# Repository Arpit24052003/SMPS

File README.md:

# SMPS
Power Supply Unit (PSU) is a vital part in any electronic product design. Most household electronic products like Mobile Chargers, Bluetooth Speakers, Power Banks, Smart Watches etc requires a Power Supply circuit that could convert the AC mains supply to 5V DC to operate them. In this project we will build a similar AC to DC power supply circuit with 10W power rating. That is our circuit will convert the 220V AC mains to 5V and provide a maximum output current upto 2A. This power rating should be enough to power most electronic products running on 5V. Also 5V 2A SMPS circuit is quite popular in electronics since there are lots of microcontrollers which operates on 5V.

The idea of the project is to keep the build as simple as possible, hence we will design the complete circuit over a dotted board (perf board) and will also build our own transformer so that anyone could replicate this design or build similar ones. Excited Right! So lets get started.

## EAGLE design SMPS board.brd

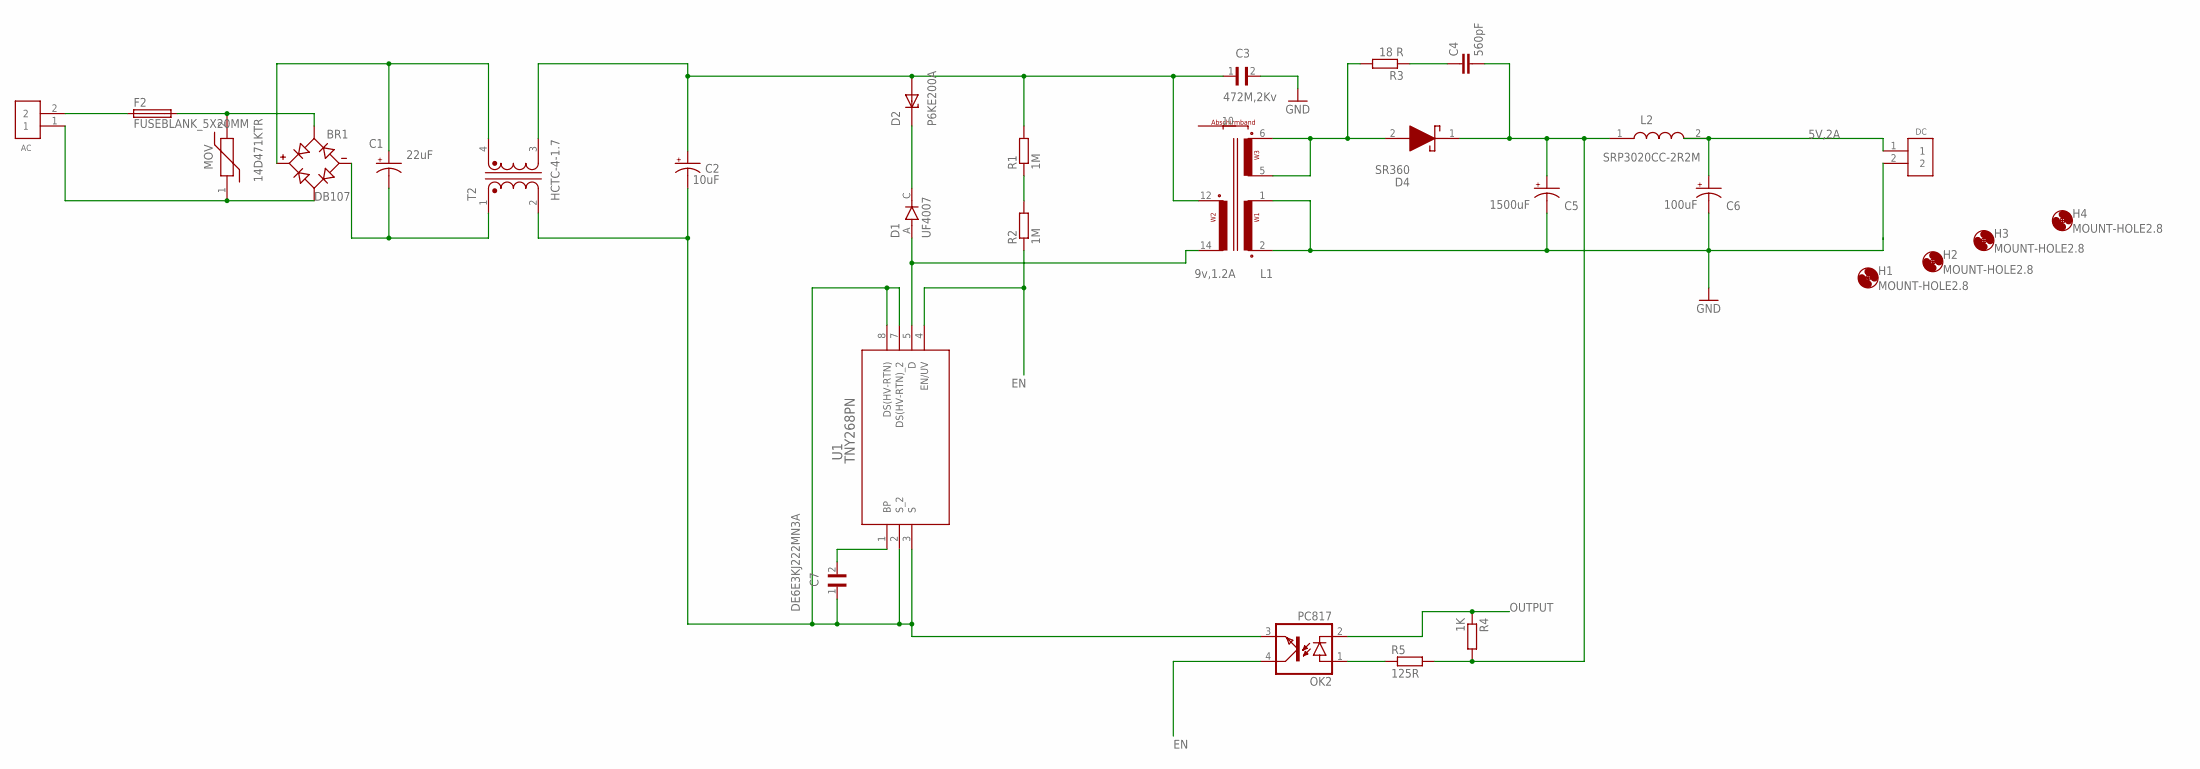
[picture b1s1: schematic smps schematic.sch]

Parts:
AC: 282837-2; TE_282837-2
BR1: DB107; DIP825W50P509L880H320Q4
C1: 22uF; CPOL-RADIAL-1F-2.7V
C2: 10uF; CPOL-RADIAL-1F-2.7V
C3: 472M,2Kv; CAP_DE6E3KJ222MN3A
C4: 560pF; C2.5-3
C5: 1500uF; CPOL-RADIAL-1F-2.7V
C6: 100uF; CPOL-RADIAL-1F-2.7V
C7: DE6E3KJ222MN3A; CAP_DE6E3KJ222MN3A
D1: UF4007; DIOAD1036W78L520D274
D2: P6KE200A; DIOAD1276W78L760D360
D4: SR360; DIOAD3020W130L900D530
DC: 282837-2; TE_282837-2
F2: FUSEBLANK_5X20MM; FUSE_HOLDER_5X20MM
H1, H2, H3, H4: MOUNT-HOLE2.8; 2,8
L1: 9v,1.2A; ST-D2
L2: SRP3020CC-2R2M; INDPM3532X200N
MOV: 14D471KTR; MOV14D471K
OK2: PC817; DIL04
R1, R2: 1M; 0204/7
R3: 18 R; 0204/7
R4: 1K; 0204/7
R5: 125R; 0204/7
T2: HCTC-4-1.7; XFMR_HCTC-4-1.7
U1: TNY268PN; PDIP-8B_P_PWI

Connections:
5V,2A: C6.+, DC.1, L2.2
EN: OK2.4 (COL), R2.1, U1.4 (EN/UV)
GND: C3.2, C5.-, C6.-, DC.2, L1.1 (1E), L1.2 (1A)
unnamed: BR1.1 (+), C1.+, T2.4
unnamed: BR1.2 (-), C1.-, T2.1
unnamed: AC.2, F2.1
unnamed: BR1.3 (AC1), F2.2, MOV.2
unnamed: AC.1, BR1.4 (AC2), MOV.1
unnamed: C2.-, C7.1, OK2.3 (EMIT), T2.2, U1.2 (S_2), U1.3 (S), U1.7 (DS(HV-RTN)_2), U1.8 (DS(HV-RTN))
unnamed: R1.1, R2.2
unnamed: C2.+, C3.1, D2.A, L1.12 (2A), R1.2, T2.3
unnamed: D1.C (K), D2.C
unnamed: D1.A, L1.14 (2E), U1.5 (D)
unnamed: C7.2, U1.1 (BP)
unnamed: D4.2 (A), L1.5 (3E), L1.6 (3A), R3.2
unnamed: C4.2, C5.+, D4.1 (K), L2.1, R4.2, R5.2
unnamed: C4.1, R3.1
unnamed: OK2.1 (A), R5.1
OUTPUT: OK2.2 (C), R4.1

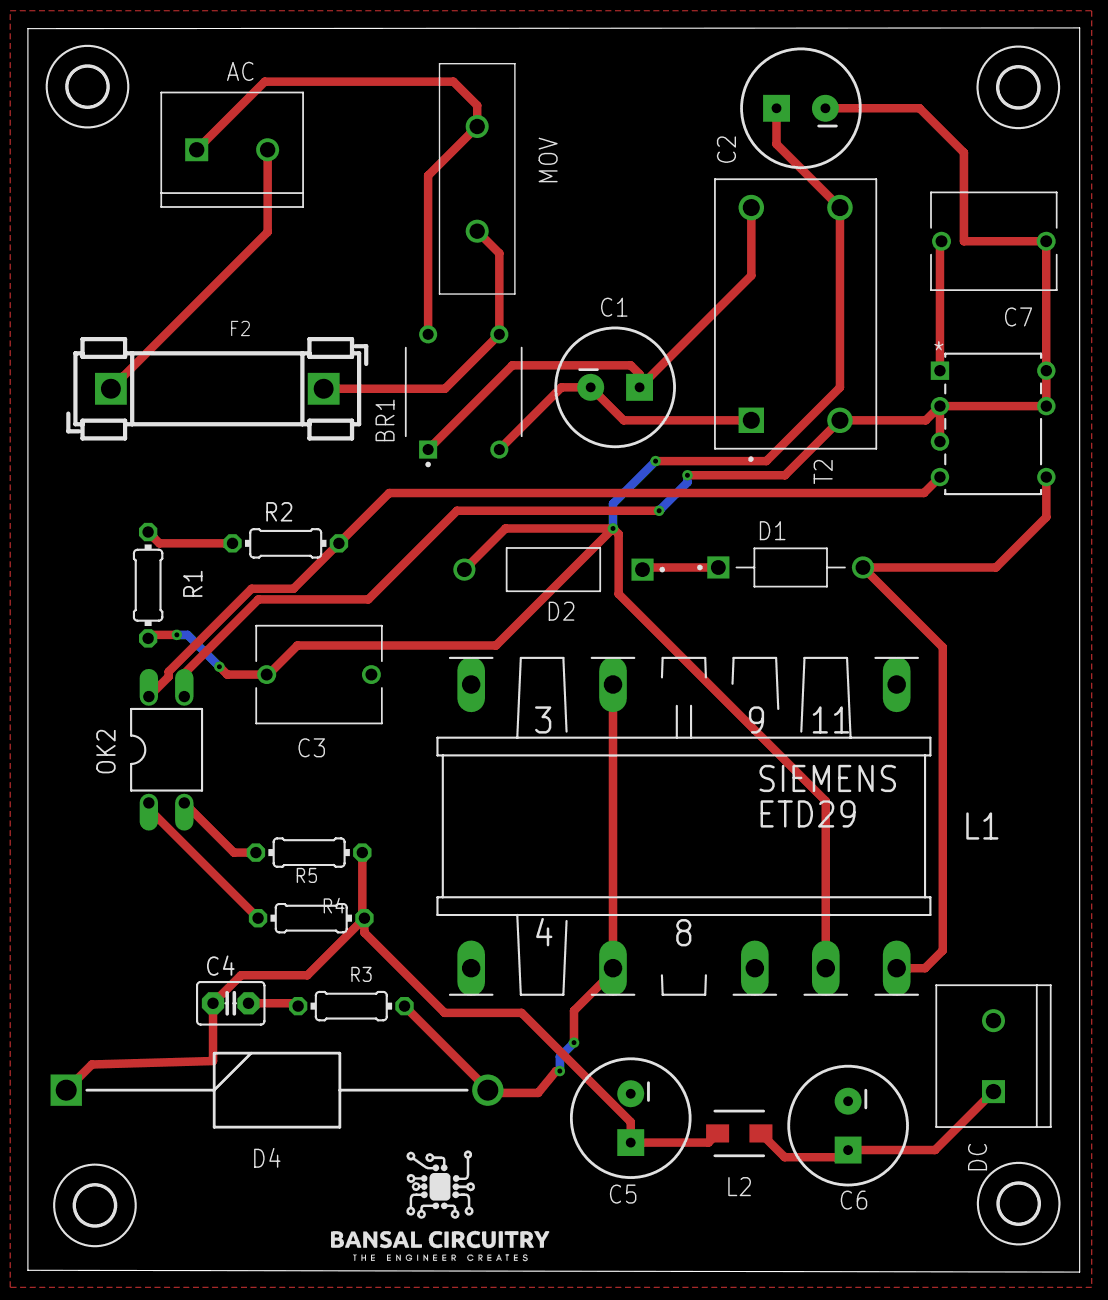
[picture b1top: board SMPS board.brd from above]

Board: 2 copper layers, 75.3 x 89.1 mm, 29 parts (0 on the bottom side), 19 nets.

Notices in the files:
parts and their libraries:
SparkFun-Capacitors: Licensing: Creative Commons ShareAlike 4.0 International - https://creativecommons.org/licenses/by-sa/4.0
COPYRIGHT: Copyright (C) 2024 Ultra Librarian. All rights reserved.
